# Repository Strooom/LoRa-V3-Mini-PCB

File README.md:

# Minimal size LoraWAN sensor node

This is a stripped-down version of https://github.com/Strooom/LoRa-V3-PCB
* no rechargeable battery - only 14250 type Li batteries 3.0 up to 3.6V
* no e-paper display
* no USB for charging
* non-volatile memory 128KByte io up to 512 KByte
* no BME68X - only SHT40 and TSL2591
* no QWIIC connector
* internal antenna with less gain
* application button is 1-way, io 3-way

KiCAD design files for the LoRa-V3-Mini PCB.

## Front render

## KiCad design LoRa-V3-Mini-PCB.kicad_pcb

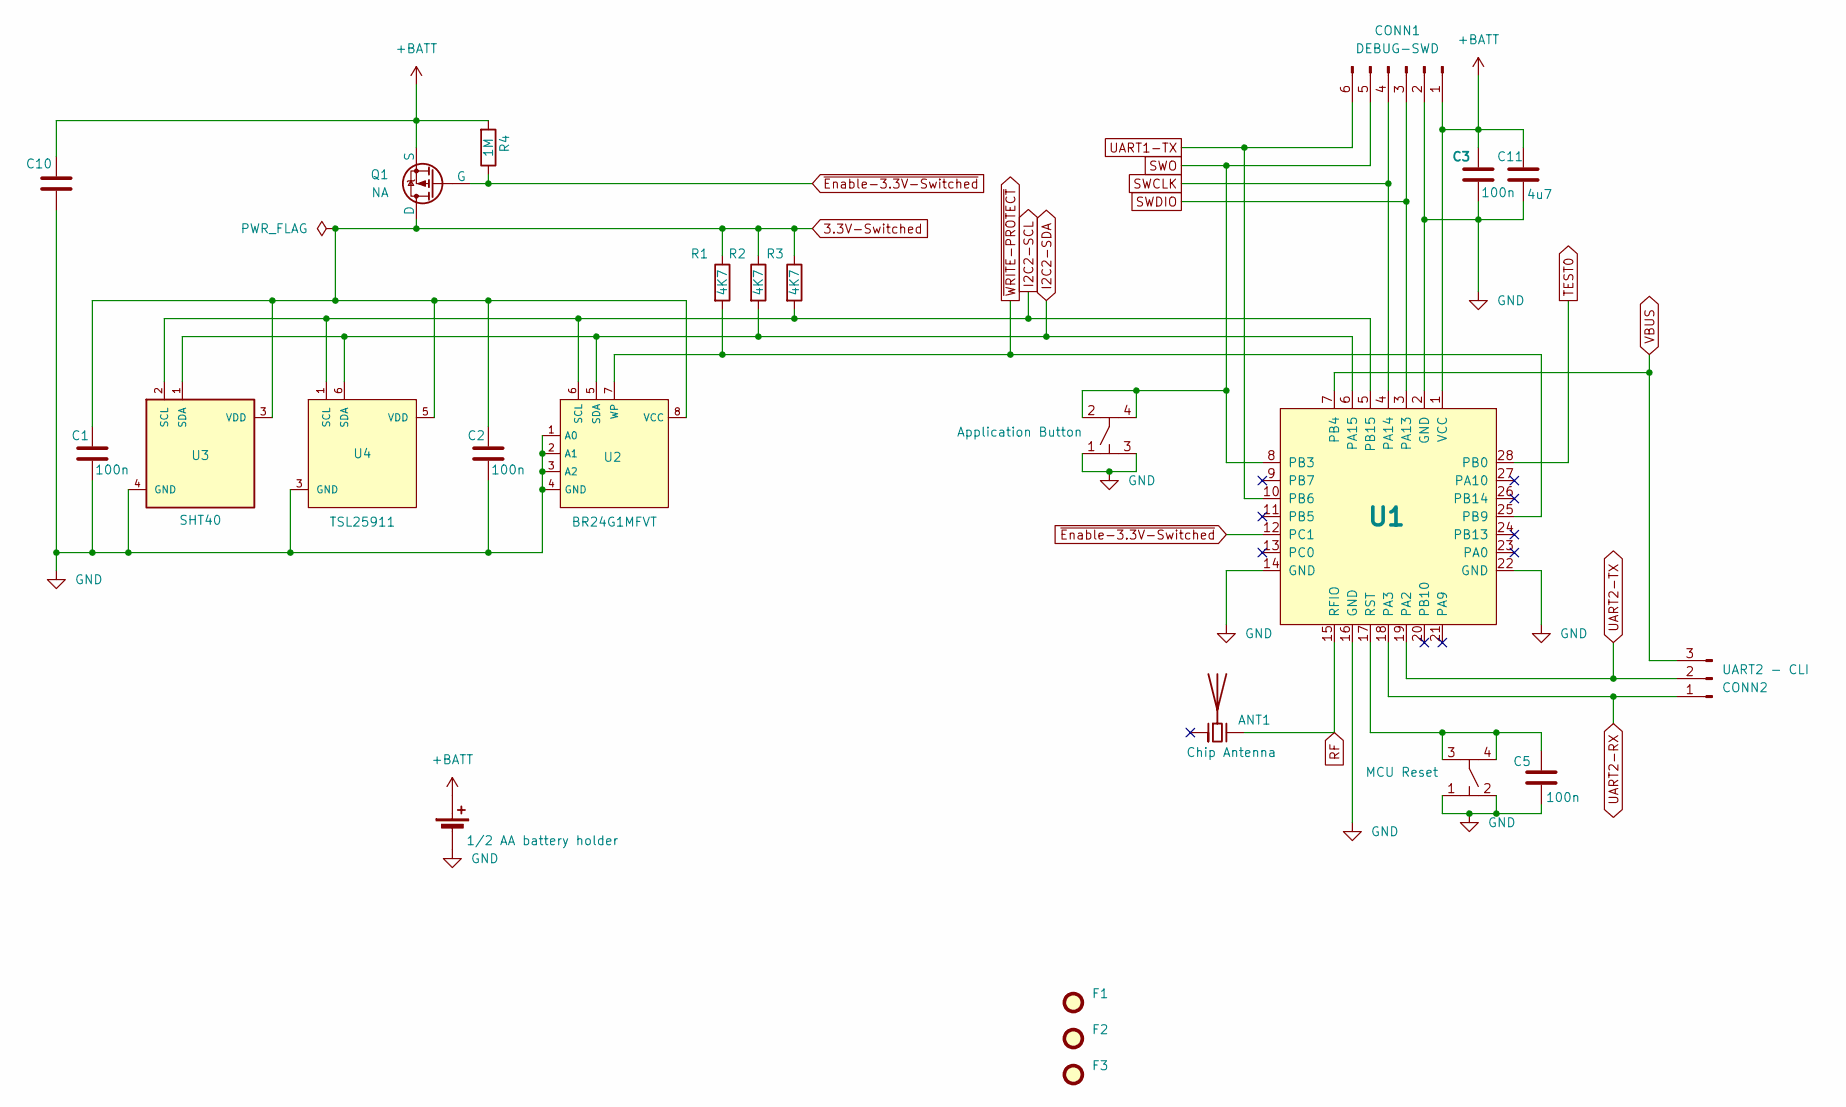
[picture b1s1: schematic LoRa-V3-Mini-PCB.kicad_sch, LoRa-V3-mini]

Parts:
ANT1: Chip Antenna; XDCR_ANT-868-CHP-T; manufacturerPartNumber ANT-868-CHP-T
BH1: Battery Holder; 108_Keystone; manufacturerPartNumber 108
C1, C2, C3, C5: 100nF; C_0603_nominal; manufacturerPartNumber CGA3E2X7R1E104K080AA
C10, C11: 4.7uF; C_0805; manufacturerPartNumber CL21B475KPFNFNE
CONN1: DEBUG-SWD; DebugConnector_1x06_P2.54mm; manufacturerPartNumber NA
CONN2: UART2 - CLI; CliConnector_3p; manufacturerPartNumber NA
F1, F2, F3: Fiducial; Fiducial_0.5mm_Mask1mm; manufacturerPartNumber NA
Q1: NA; SI2367DS-SOT-23; manufacturerPartNumber SI2367DS-T1-GE3
R1, R2, R3: 4K7; R_0603_nominal; manufacturerPartNumber CR0603-FX-4701ELF
R4: 330K; R_0603_nominal; manufacturerPartNumber AC0603JR-07330KL
SW1: Application Button; 4343X10458XX; manufacturerPartNumber 434331045822
SW2: MCU Reset; 4341330258X6; manufacturerPartNumber 434133025816
U1: Seeed_Wio-E5 LE; LoRa-E5; manufacturerPartNumber 114993121
U2: BR24G1MFVT; BR24G1M-TSSOP-B8; manufacturerPartNumber BR24G1MFVT-5AE2
U3: SHT40; SHT4X; manufacturerPartNumber SHT40-BD1B-R2
U4: TSL25911; TSL2591-SON; manufacturerPartNumber TSL25911FN

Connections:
3.3V-Switched: C1.1, C2.1, Q1.3 (D), R1.1, R2.1, R3.1, U2.8 (VCC), U3.3 (VDD), U4.5 (VDD)
+BATT: BH1.1 (+), C3.1, C10.1, C11.1, CONN1.1, Q1.2 (S), R4.2, U1.1 (VCC)
GND: BH1.2 (-), C1.2, C2.2, C3.2, C5.2, C10.2, C11.2, CONN1.2, SW1.1, SW1.3, SW2.1, SW2.2, U1.2 (GND), U1.14 (GND), U1.16 (GND), U1.22 (GND), U2.1 (A0), U2.2 (A1), U2.3 (A2), U2.4 (GND), U3.4 (GND), U4.3 (GND)
I2C2-SCL: R3.2, U1.5 (PB15), U2.6 (SCL), U3.2 (SCL), U4.1 (SCL)
I2C2-SDA: R2.2, U1.6 (PA15), U2.5 (SDA), U3.1 (SDA), U4.6 (SDA)
unnamed: C5.1, SW2.3, SW2.4, U1.17 (RST)
RF: ANT1.1 (FEED), U1.15 (RFIO)
SWCLK: CONN1.4, U1.4 (PA14)
SWDIO: CONN1.3, U1.3 (PA13)
SWO: CONN1.5, SW1.2, SW1.4, U1.8 (PB3)
TEST0: U1.28 (PB0)
UART1-TX: CONN1.6, U1.10 (PB6)
UART2-RX: CONN2.1, U1.18 (PA3)
UART2-TX: CONN2.2, U1.19 (PA2)
VBUS: CONN2.3, U1.7 (PB4)
~Enable-3.3V-Switched: Q1.1 (G), R4.1, U1.12 (PC1)
~WRITE-PROTECT: R1.2, U1.25 (PB9), U2.7 (WP)

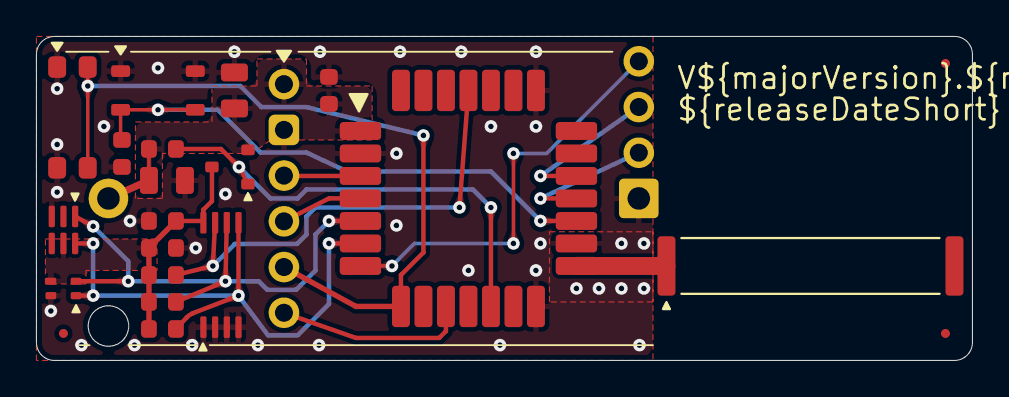
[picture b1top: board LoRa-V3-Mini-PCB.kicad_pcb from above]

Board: 2 copper layers, 52.0 x 18.0 mm, 24 parts (1 on the bottom side), 16 nets.

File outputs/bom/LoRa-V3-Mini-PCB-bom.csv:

Row,Description,Part,References,Value,Footprint,Quantity Per PCB,Status,Datasheet,manufacturerName,manufacturerPartNumber,octopartUrl,GPN,digikeyPartNumber,mouserPartNumber
1,Ceramic chip antenna,Antenna_Chip,ANT1,ANT-868-CHP-T,XDCR_ANT-868-CHP-T,1, ,https://www.mouser.be/datasheet/2/418/9/lnncs00024_1-3238509.pdf,TE Connectivity Linx,ANT-868-CHP-T,https://octopart.com/search?q=ANT-868-CHP-T&currency=USD&specs=0,NA,ANT-868-CHP-TCT-ND,712-ANT-868-CHP-T
2,1/2 AA battery holder,Battery_Cell,BH1,108,108_Keystone,1, ,https://www.mouser.be/datasheet/2/215/108-745412.pdf,KeyStone,108,https://octopart.com/108-keystone-11058,NA,36-108-ND,534-108
3,4u7,C,C10 C11,C1608X7S1A475K080AC,C_0805,2, ,https://product.tdk.com/system/files/dam/doc/product/capacit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,TDK,C1608X7S1A475K080AC,https://octopart.com/c1608x7s1a475k080ac-tdk-28168672?r=sp,GPC0603475-10-X7S,445-14258-1-ND,810-C1608X7S1A475KAC
4,100n,C,C1 C2 C3 C5,CGA3E2X7R1E104K080AA,C_0603_nominal,4, ,https://octopart.com/datasheet/cga3e2x7r1e104k080aa-tdk-25947977,TDK,CGA3E2X7R1E104K080AA,https://octopart.com/cga3e2x7r1e104k080aa-tdk-25947977?r=sp,GPC0603104-25-X7R,445-5667-1-ND,810-CGA3E2X7R1E104K
5,"Generic connector, single row, 01x06, script generated",DebugConnector-6p,CONN5,DEBUG-SWD,DebugConnector_1x06_P2.54mm,1, ,~,NA,NA,NA,NA,NA,NA
6,P-Channel MOSFET,Si2367DS,Q1,SI2367DS-T1-GE3,SI2367DS-SOT-23,1, ,https://www.vishay.com/docs/65015/si2367ds.pdf,Vishay Siliconix,SI2367DS-T1-GE3,https://octopart.com/si2367ds-t1-ge3-vishay-42637886?r=sp,NA,SI2367DS-T1-GE3TR-ND,781-SI2367DS-GE3
7,1M,R,R4,CR0603-FX-1004ELF,R_0603_nominal,1, ,https://octopart.com/datasheet/cr0603-fx-1004elf-bourns-3899435,Bourns,CR0603-FX-1004ELF,https://octopart.com/cr0603-fx-1004elf-bourns-3899435?r=sp,GPR06031M,CR0603-FX-1004ELFCT-ND,652-CR0603FX-1004ELF
8,4K7,R,R1 R2 R3,CR0603-FX-4701ELF,R_0603_nominal,3, ,https://octopart.com/datasheet/cr0603-fx-4701elf-bourns-3867100,Bourns,CR0603-FX-4701ELF,https://octopart.com/cr0603-fx-4701elf-bourns-3867100?r=sp,GPR06034K7,CR0603-FX-4701ELFCT-ND,652-CR0402FX-4701GLF
9,MCU Reset,Switch_435451019820,SW2,434331045816,4341330258X6,1, ,,Wurth Electronics,434331045816,,NA,,
10,Application buttonswitch,Switch_434331045822,SW1,434331045822,4343X10458XX,1, ,https://www.we-online.com/katalog/datasheet/434331045822.pdf,Wurth Electronics,434133025816,https://octopart.com/434331045822-wurth+elektronik-22866031?r=sp,NA,732-7055-1-ND,710-434331045822
11,Wio-E5-LE-HF,Seeed_Wio-E5,U1,114993121,LoRa-E5,1, ,https://files.seeedstudio.com/products/114993120/Wio-E5-LE%2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,Seeed Technology,114993121,https://octopart.com/114993121-seeed+studio-142683940?r=sp,NA,1597-114993121-ND,713-114993121
12,EEPROM SERIAL EEPROM,BR24G1MFVT,U2,BR24G1MFVT,BR24G1M-TSSOP-B8,1, ,https://fscdn.rohm.com/en/products/databook/datasheet/ic/mem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,ROHM,BR24G1MFVT-5AE2,https://octopart.com/br24g1mfvt-5ae2-rohm-126430213?r=sp,NA,846-BR24G1MFVT-5AE2CT-ND,755-BR24G1MFVT-5AE2
13,Digital Relative Humidity Temperature Sensor,SHT40,U3,SHT40,SHT4X,1, ,https://www.mouser.be/datasheet/2/682/Sensirion_Datasheet_SH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,Sensirion,SHT40-BD1B-R2,https://octopart.com/sht40-bd1b-r2-sensirion-137454263?r=sp,NA,1649-SHT40-BD1B-R2CT-ND,403-SHT40-AD1F-R2
14,Light to Digital Converters Hi-Sensitvty Ambient Light Sensor IC,TSL2591,U4,TSL25911,TSL2591-SON,1, ,https://ams.com/documents/20143/36005/TSL2591_DS000338_6-00.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,ams Osram,TSL25911FN,https://octopart.com/tsl25911fn-osram-126135547?r=sp,NA,TSL25911FNCT-ND,985-TSL25911FN





Project info:
Schematic:,LoRa-V3-Mini-PCB
Variant:,default
Revision:,V1.2
Date:,2024-07-26
KiCad Version:,8.0.8+1
Statistics:
Component Groups:,14
Component Count:,20
Fitted Components:,20
Number of PCBs:,1
Total Components:,20

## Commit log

2024-09-23 add schematic in pdf format
2024-09-23 adding a CI/CD workflow for KiCAD
2024-09-23 Update drcerc.yml
    trying to export pdf schematic
2024-09-23 new attempt using kiBOT
2024-09-23 upgrade to uploadv4
2024-09-23 corrected workflow for actual filenames
2024-09-23 experiment001
    enable more verbosity
2024-09-23 experiment002
    simplifies kibot config file
2024-09-23 experiment003
    add preflight check to kibot config
2024-09-23 experiment004
    corrected the tag for KiBOT github action
2024-09-23 experiment005
    adding some outputs
2024-09-27 add blender rendering to KiBOT outputs
2024-10-09 update the workflow .yml files
2024-10-09 upgrade gitignore
2024-10-09 add workflow generated files
2024-10-09 move global components into project library
2024-10-09 update 3d models / footprints
2024-10-09 using project lib io global
2024-10-09 update libraries
2024-10-10 update application switch
2025-01-24 upgraded debug connector with UART1TX
2025-01-25 fix 3d-models
2025-01-25 finishing touch to layout
2025-01-28 add saft 14250 model to footprint
    to improve exported step file before designing an enclosure
2025-01-28 save file
2025-02-24 change caps to 0805
2025-02-24 fix BOM
2025-02-24 add extra csv file for kicost
2025-02-24 try fix error on GND needing datasheet...
2025-02-24 upgrade workflow to latest version of kibot
2025-02-24 rename GPN to genericPartNumber
2025-02-24 exclude conn5 from BOM
2025-02-24 move decouple cap closer to MCU
2025-03-06 Add Pads for CLI connector
2025-03-11 exclude kicost workflow files FTTB
2025-03-11 remove files from git
2025-03-11 major Major release v1.0
2025-03-11 Major major release V1.0
2025-03-11 Major major - release V1.0
2025-03-12 workflow improvements
    reactivate step file output
    correct blender rendering for double output
2025-03-12 move custom bridges for Aisler to other layer
2025-03-12 exclude kicost files from being tracked until a CI solution is working
2025-03-19 update bom
2025-06-02 add VBUS to detect CLI
2025-06-02 fix datasheet for CLI connector
